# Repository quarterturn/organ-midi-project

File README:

This is the project repository for the 2012 Maker Faire project MIDIfying Old Organs

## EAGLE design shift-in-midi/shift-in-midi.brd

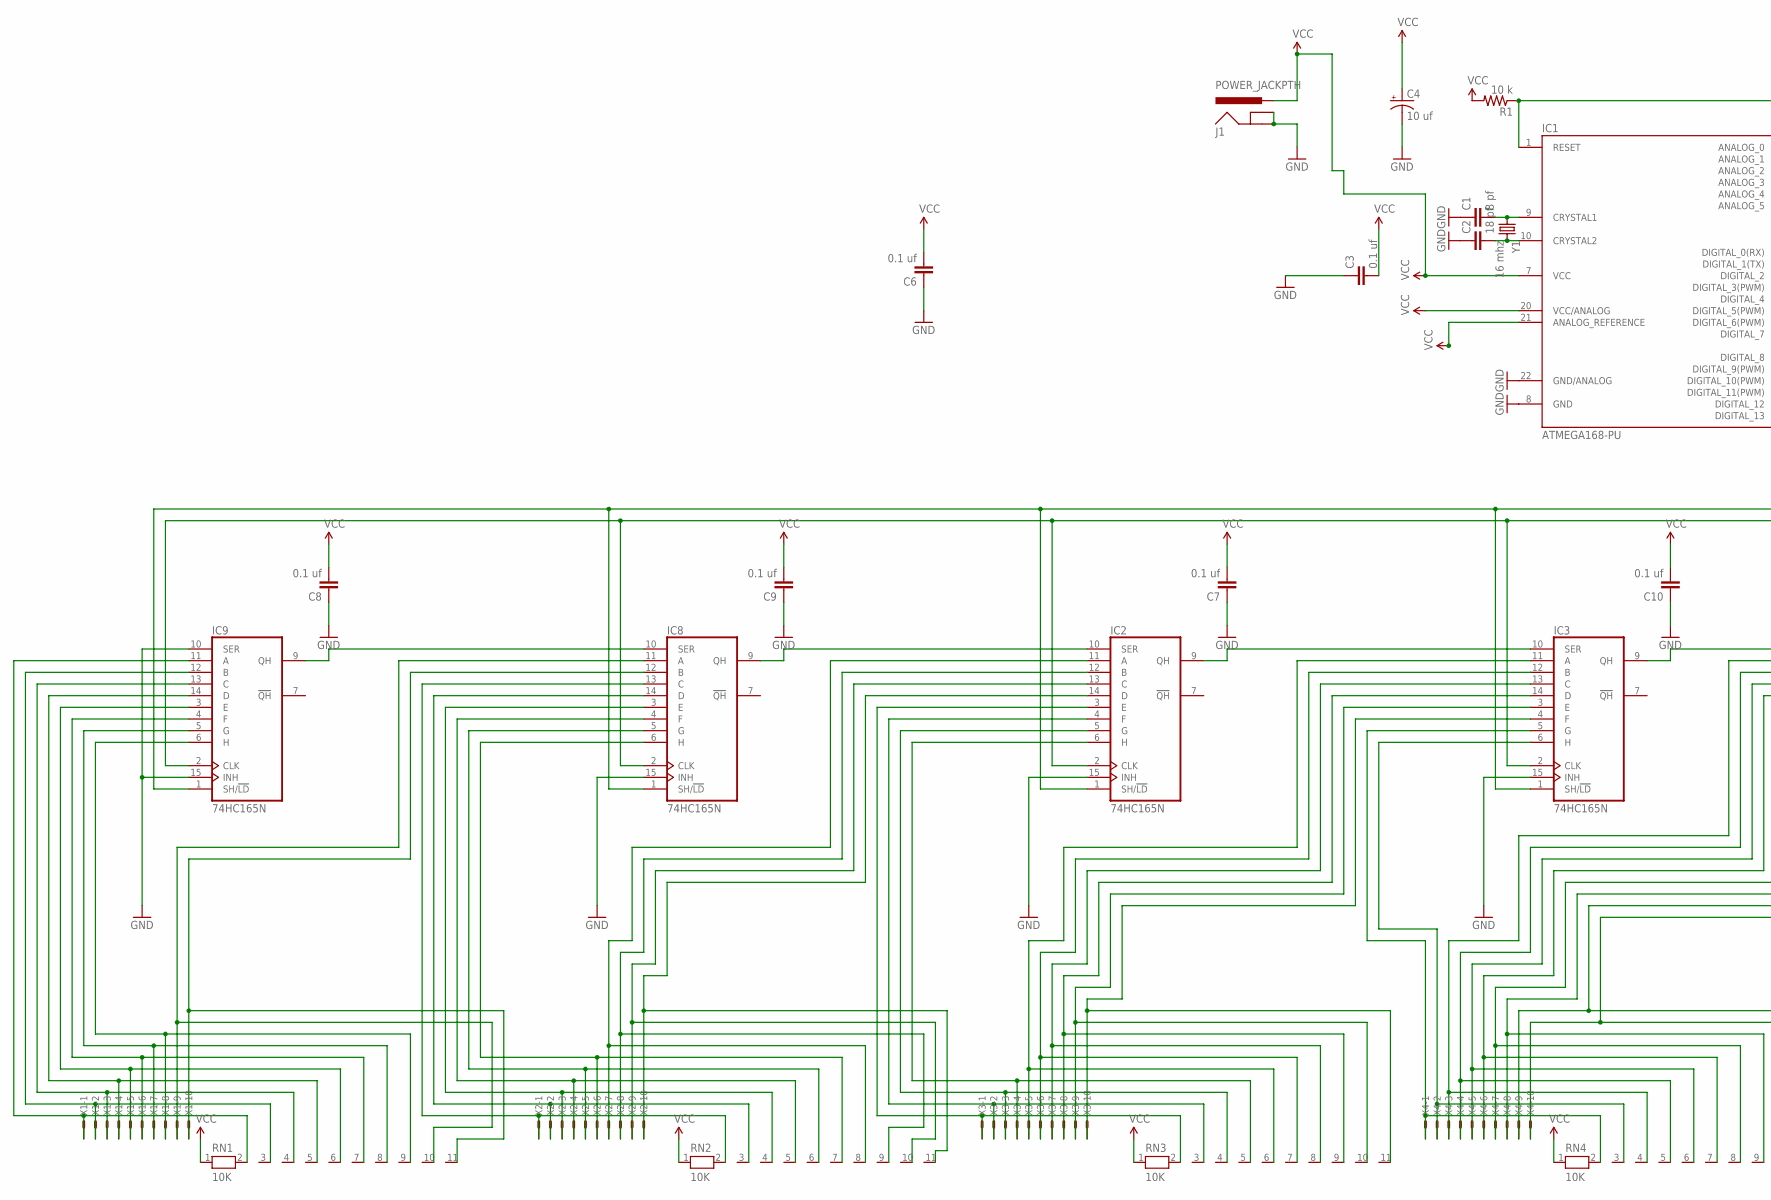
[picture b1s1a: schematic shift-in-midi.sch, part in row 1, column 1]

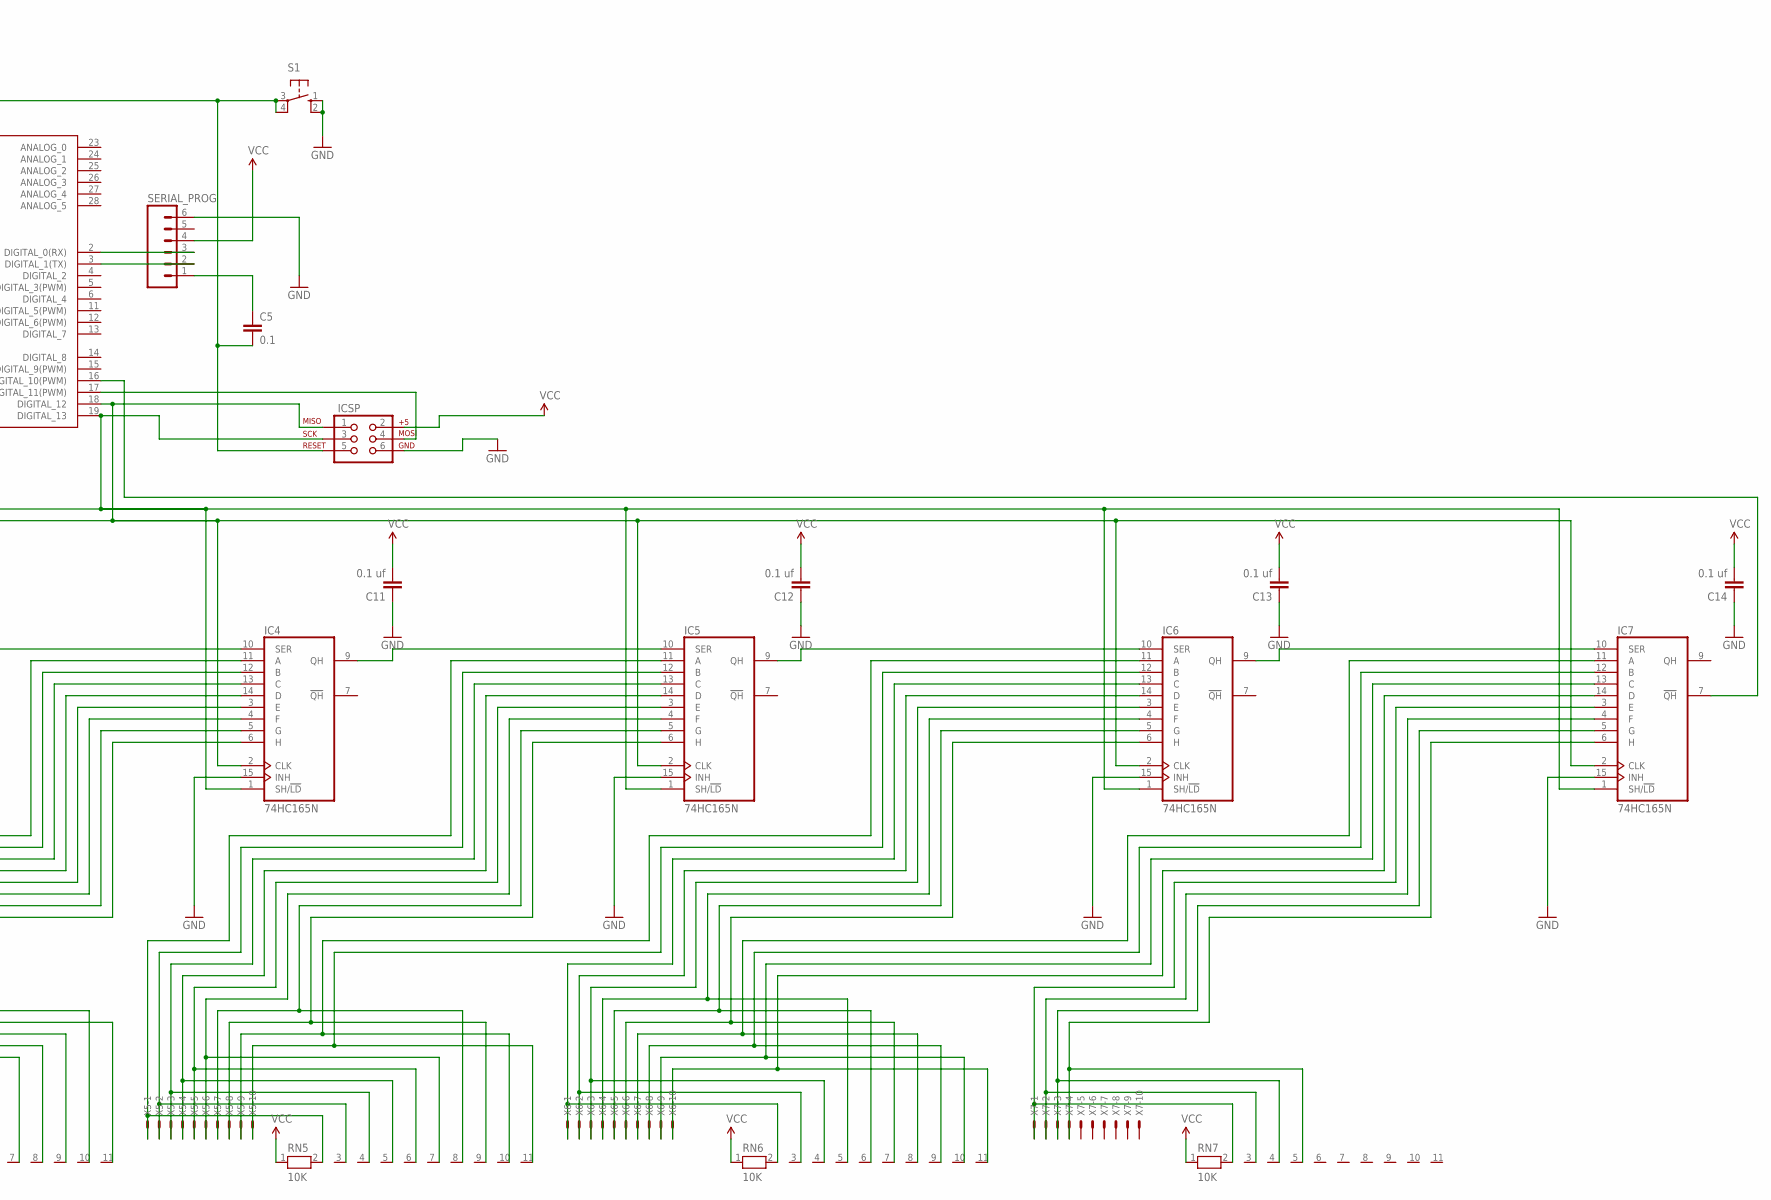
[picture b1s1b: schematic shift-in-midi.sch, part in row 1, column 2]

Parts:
C1: 8 pf; CAP-PTH-SMALL2
C2: 18 pf; CAP-PTH-SMALL2
C3, C6, C7, C8, C9, C10, C11, C12, C13, C14: 0.1 uf; CAP-PTH-SMALL2
C4: 10 uf; CPOL-RADIAL-10UF-25V
C5: 0.1; CAP-PTH-SMALL
IC1: ATMEGA168-PU; DIL28-3
IC2, IC3, IC4, IC5, IC6, IC7, IC8, IC9: 74HC165N; DIL16
ICSP: AVR_SPI_PRG_62X3_LOCK; 2X3_LOCK
J1: POWER_JACKPTH; POWER_JACK_PTH
R1: 10 k; AXIAL-0.4
RN1, RN2, RN3, RN4, RN5, RN6, RN7: 10K; RN-11
S1: 10-XX; B3F-10XX
SERIAL_PROG: M06LONGPADS; 1X06_LONGPADS
X1, X2, X3, X4, X5, X6, X7: KK-156-10
Y1: 16 mhz; HC49US

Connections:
GND: C1.1, C2.1, C3.1, C4.2 (-), C6.1, C7.1, C8.1, C9.1, C10.1, C11.1, C12.1, C13.1, C14.1, IC1.8 (GND), IC1.22 (GND/ANALOG), IC2.8 (GND), IC2.15 (INH), IC3.8 (GND), IC3.15 (INH), IC4.8 (GND), IC4.15 (INH), IC5.8 (GND), IC5.15 (INH), IC6.8 (GND), IC6.15 (INH), IC7.8 (GND), IC7.15 (INH), IC8.8 (GND), IC8.15 (INH), IC9.8 (GND), IC9.10 (SER), IC9.15 (INH), ICSP.6, J1.GND, J1.GNDBREAK, S1.1 (S), S1.2 (S1), SERIAL_PROG.6
unnamed: C5.2, IC1.1 (RESET), ICSP.5, R1.P$1 (1), S1.3, S1.4 (P1)
unnamed: IC1.19 (DIGITAL_13), IC2.1 (SH/!LD), IC3.1 (SH/!LD), IC4.1 (SH/!LD), IC5.1 (SH/!LD), IC6.1 (SH/!LD), IC7.1 (SH/!LD), IC8.1 (SH/!LD), IC9.1 (SH/!LD), ICSP.3
unnamed: C1.2, IC1.9 (CRYSTAL1), Y1.1
unnamed: C2.2, IC1.10 (CRYSTAL2), Y1.2
unnamed: IC8.10 (SER), IC9.9 (QH)
unnamed: IC2.10 (SER), IC8.9 (QH)
unnamed: C5.1, SERIAL_PROG.1
unnamed: IC1.18 (DIGITAL_12), IC2.2 (CLK), IC3.2 (CLK), IC4.2 (CLK), IC5.2 (CLK), IC6.2 (CLK), IC7.2 (CLK), IC8.2 (CLK), IC9.2 (CLK), ICSP.1
unnamed: IC1.2 (DIGITAL_0(RX)), SERIAL_PROG.3
unnamed: IC1.3 (DIGITAL_1(TX)), SERIAL_PROG.2
unnamed: IC2.9 (QH), IC3.10 (SER)
unnamed: IC3.9 (QH), IC4.10 (SER)
unnamed: IC4.9 (QH), IC5.10 (SER)
unnamed: IC5.9 (QH), IC6.10 (SER)
unnamed: IC6.9 (QH), IC7.10 (SER)
unnamed: IC1.17 (DIGITAL_11(PWM)), ICSP.4
unnamed: IC1.16 (DIGITAL_10(PWM)), IC7.7 (!QH)
unnamed: IC9.11 (A), RN1.2, X1.1
unnamed: IC9.12 (B), RN1.3, X1.2
unnamed: IC9.13 (C), RN1.4, X1.3
unnamed: IC8.12 (B), RN1.11, X1.10
unnamed: IC9.3 (E), RN1.6, X1.5
unnamed: IC9.4 (F), RN1.7, X1.6
unnamed: IC9.5 (G), RN1.8, X1.7
unnamed: IC9.6 (H), RN1.9, X1.8
unnamed: IC8.11 (A), RN1.10, X1.9
unnamed: IC8.13 (C), RN2.2, X2.1
unnamed: IC8.14 (D), RN2.3, X2.2
unnamed: IC8.3 (E), RN2.4, X2.3
unnamed: IC8.4 (F), RN2.5, X2.4
unnamed: IC8.5 (G), RN2.6, X2.5
unnamed: IC4.6 (H), RN4.11, X4.10
unnamed: IC2.11 (A), RN2.8, X2.7
unnamed: IC2.12 (B), RN2.9, X2.8
unnamed: IC2.13 (C), RN2.10, X2.9
unnamed: IC2.14 (D), RN2.11, X2.10
unnamed: IC2.3 (E), RN3.2, X3.1
unnamed: IC2.4 (F), RN3.3, X3.2
unnamed: IC2.5 (G), RN3.4, X3.3
unnamed: IC2.6 (H), RN3.5, X3.4
unnamed: IC3.11 (A), RN3.6, X3.5
unnamed: IC3.12 (B), RN3.7, X3.6
unnamed: IC3.13 (C), RN3.8, X3.7
unnamed: IC3.14 (D), RN3.9, X3.8
unnamed: IC3.3 (E), RN3.10, X3.9
unnamed: IC3.4 (F), RN3.11, X3.10
unnamed: IC3.5 (G), RN4.2, X4.1
unnamed: IC3.6 (H), RN4.3, X4.2
unnamed: IC4.11 (A), RN4.4, X4.3
unnamed: IC4.12 (B), RN4.5, X4.4
unnamed: IC4.13 (C), RN4.6, X4.5
unnamed: IC4.14 (D), RN4.7, X4.6
unnamed: IC4.3 (E), RN4.8, X4.7
unnamed: IC4.4 (F), RN4.9, X4.8
unnamed: IC4.5 (G), RN4.10, X4.9
unnamed: IC5.11 (A), RN5.2, X5.1
unnamed: IC5.12 (B), RN5.3, X5.2
unnamed: IC5.13 (C), RN5.4, X5.3
unnamed: IC5.14 (D), RN5.5, X5.4
unnamed: IC5.3 (E), RN5.6, X5.5
unnamed: IC5.4 (F), RN5.7, X5.6
unnamed: IC5.5 (G), RN5.8, X5.7
unnamed: IC5.6 (H), RN5.9, X5.8
unnamed: IC6.11 (A), RN5.10, X5.9
unnamed: IC6.12 (B), RN5.11, X5.10
unnamed: IC6.13 (C), RN6.2, X6.1
unnamed: IC6.14 (D), RN6.3, X6.2
unnamed: IC6.3 (E), RN6.4, X6.3
unnamed: IC6.4 (F), RN6.5, X6.4
unnamed: IC6.5 (G), RN6.6, X6.5
unnamed: IC6.6 (H), RN6.7, X6.6
unnamed: IC7.11 (A), RN6.8, X6.7
unnamed: IC7.12 (B), RN6.9, X6.8
unnamed: IC7.13 (C), RN6.10, X6.9
unnamed: IC7.14 (D), RN6.11, X6.10
unnamed: IC7.3 (E), RN7.2, X7.1
unnamed: IC7.4 (F), RN7.3, X7.2
unnamed: IC7.5 (G), RN7.4, X7.3
unnamed: IC7.6 (H), RN7.5, X7.4
unnamed: IC9.14 (D), RN1.5, X1.4
unnamed: IC8.6 (H), RN2.7, X2.6
VCC: C3.2, C4.1 (+), C6.2, C7.2, C8.2, C9.2, C10.2, C11.2, C12.2, C13.2, C14.2, IC1.7 (VCC), IC1.20 (VCC/ANALOG), IC1.21 (ANALOG_REFERENCE), IC2.16 (VCC), IC3.16 (VCC), IC4.16 (VCC), IC5.16 (VCC), IC6.16 (VCC), IC7.16 (VCC), IC8.16 (VCC), IC9.16 (VCC), ICSP.2, J1.PWR, R1.P$2 (2), RN1.1, RN2.1, RN3.1, RN4.1, RN5.1, RN6.1, RN7.1, SERIAL_PROG.4

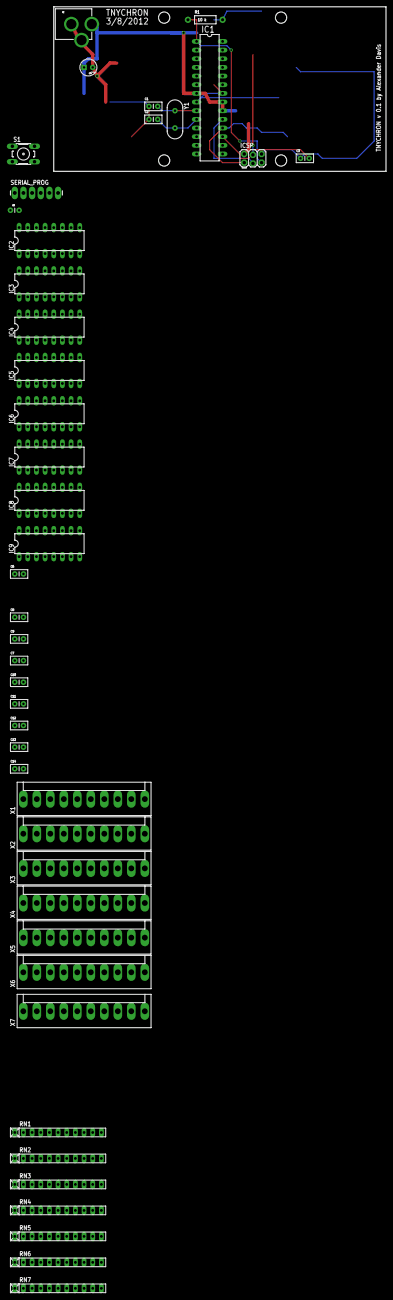
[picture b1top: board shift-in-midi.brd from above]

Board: 2 copper layers, 97.5 x 48.2 mm, 47 parts (0 on the bottom side), 83 nets.

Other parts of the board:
U$4, U$5, U$6, U$7: STAND-OFF

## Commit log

2012-05-10 Fixed libraries "Fluxamasynth" and "HpDecVfd" to work with Arduino 1.0
2012-05-28 arduino code version 0.0.3
    This version is tested and working.
2012-05-29 V 0.0.4 Cleaned up comments - removed test code - removed reference to display not used in this version
2012-06-07 added Eagle schematic
2012-06-11 added description document
2012-06-14 v 0.0.4 with vfd and pot/button control panel
2012-06-14 update to section on velocity sensing and RAM
2012-06-14 minor edits

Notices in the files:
parts and their libraries:
SparkFun: Licensing: CC v3.0 Share-Alike You are welcome to use this library for commercial purposes.
